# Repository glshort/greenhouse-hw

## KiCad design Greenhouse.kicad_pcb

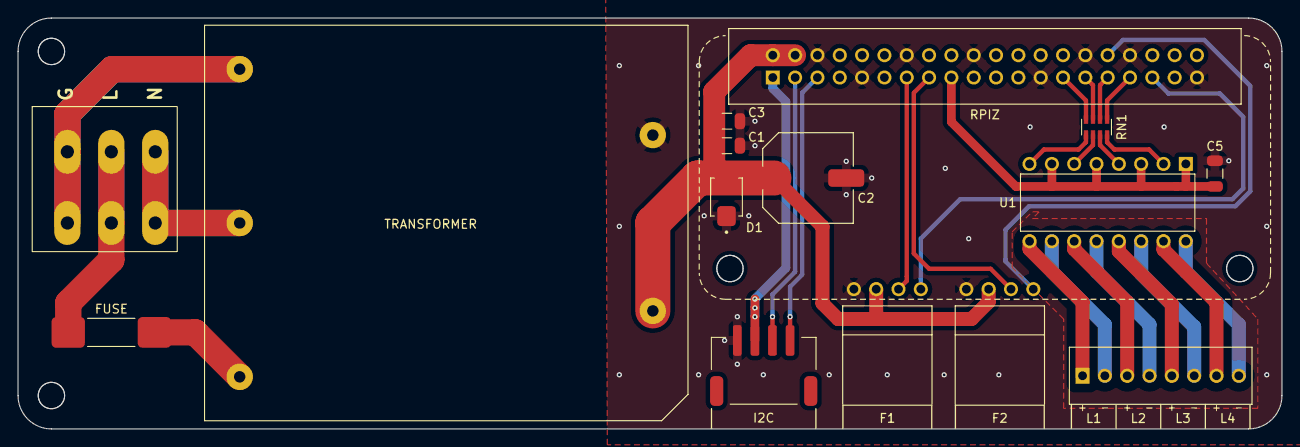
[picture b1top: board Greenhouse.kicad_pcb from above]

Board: 2 copper layers, 143.8 x 46.8 mm, 15 parts (0 on the bottom side), 29 nets.

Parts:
C1: 1µF; CAPC3216X180N
C2: 330µF; CAP_EEEFT1H331AP
C3, C5: .1µF; CAPC3216X180N
D1: D_Zener; DIOM4336X265N
F1, F2: Conn_01x03; Fan Header 3,4-pin through hole right angle, custom
FUSE: Fuse; SF-3812TM200T-2
I2C: Conn_01x04; JST_S4B-PH-SM4-TB, custom
J1: Conn_01x03; 2604-1103
J2: 282834-8; TE_282834-8, custom
RN1: CAY16-271J4LF; RESCAF80P320X160X60-8N
RPIZ: Conn_02x20_Odd_Even; Raspi Zero W Socket TH
TRANSFORMER: LD05-23B05R2-M
U1: LTV-847S; DIP880W50P254L2034H450Q16

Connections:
+3V3: C5.1, I2C.2, RPIZ.1, RPIZ.17, U1.1, U1.3, U1.5, U1.7
+5V: C1.1, C2.1, C3.1, D1.1 (K), F1.3, F2.3, RPIZ.2, RPIZ.4, TRANSFORMER.4 (+V)
Earth: J1.1, TRANSFORMER.1 (EARTH)
GND: C1.2, C2.2, C3.2, C5.2, D1.2 (A), F1.4, F2.4, I2C.1, RPIZ.6, RPIZ.9, RPIZ.14, RPIZ.20, RPIZ.25, RPIZ.30, RPIZ.34, RPIZ.39, TRANSFORMER.5 (-V)
GPIO0: RN1.4, RPIZ.27
GPIO5: RN1.3, RPIZ.29
GPIO6: RN1.2, RPIZ.31
GPIO13: RN1.1, RPIZ.33
GPIO22: F2.2, RPIZ.15
GPIO27: F1.2, RPIZ.13
LINE: FUSE.2, J1.2
NEUT: J1.3, TRANSFORMER.2 (AC(N))
unnamed: J2.1, U1.9
unnamed: J2.2, U1.10
unnamed: J2.3, U1.11
unnamed: J2.4, U1.12
unnamed: J2.5, U1.13
unnamed: J2.6, U1.14
unnamed: J2.7, U1.15
unnamed: J2.8, U1.16
unnamed: RN1.5, U1.8
unnamed: RN1.6, U1.6
unnamed: RN1.7, U1.4
unnamed: RN1.8, U1.2
unnamed: FUSE.1, TRANSFORMER.3 (AC(L))
PWM0: F2.1, RPIZ.32
PWM1: F1.1, RPIZ.35
SCL1: I2C.4, RPIZ.5
SDA1: I2C.3, RPIZ.3

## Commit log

2023-09-01 Initial commit with schematic/layout WIP
2023-09-01 Deleted previous gerber zip
2023-09-02 Added a bunch of models
2023-09-02 Updated/attached footprint models
2023-09-02 removed unused models
2023-09-02 add OS & temp editor files to gitignore
2023-09-02 updated schematic & pcb with latest part selections
2023-09-07 Finalized PCB layout, updated/added footprint models
2023-09-12 Added customized footprints for the three edge headers to include guide marks, fixed bug with GPIO net labels
2023-09-28 Adjusted footprint from actual part
2023-09-28 Final PCB adjustments from footprint changes and added stitching vias
2023-09-28 adjusted some text sizes
